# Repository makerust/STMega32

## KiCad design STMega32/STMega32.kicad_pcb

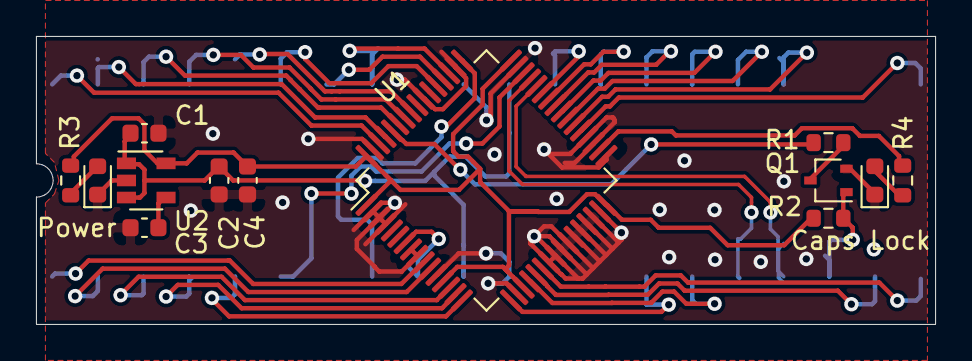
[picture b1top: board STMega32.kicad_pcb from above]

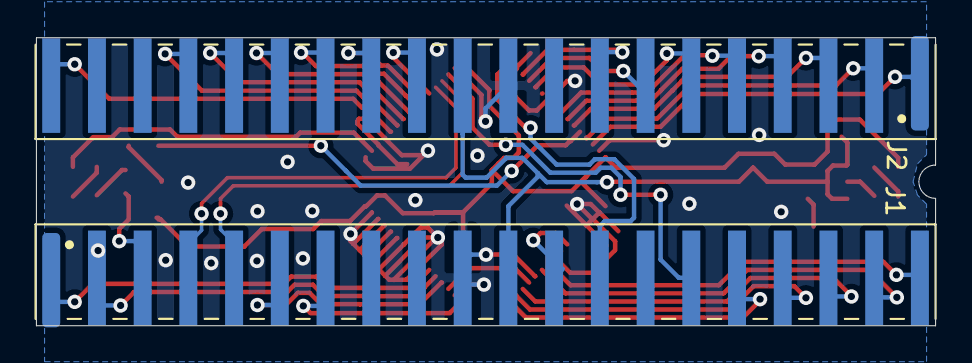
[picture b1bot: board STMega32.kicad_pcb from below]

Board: 2 copper layers, 49.9 x 16.0 mm, 15 parts (2 on the bottom side), 39 nets.

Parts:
C1, C4: 1uF; C_0603_1608Metric
C2, C3: 10nF; C_0603_1608Metric
Caps Lock: LED_ALT; LED_0603_1608Metric
J1, J2: Conn_01x20; Header_20Pin_90DegTHT_asSMD
Power: LED_ALT; LED_0603_1608Metric
Q1: 2SC4213; SOT-323_SC-70
R1, R2: 4k; R_0603_1608Metric
R3, R4: 560; R_0603_1608Metric
U1: STM32F072RBTx; LQFP-64_10x10mm_P0.5mm
U2: LD3985M33R_SOT23; SOT-23-5

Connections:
+3_3v: C4.1, R2.2, R3.1, U1.1, U1.13, U1.19, U1.32, U1.48, U1.64, U2.5
+5v: C1.1, C2.1, J1.11, J2.11, U2.1, U2.3
CAPS_LED: R4.1, U1.34
GND: C1.2, C2.2, C3.2, C4.2, Caps Lock.1, J1.10, J2.10, Power.1, Q1.2, U1.2, U1.3, U1.4, U1.8, U1.9, U1.12, U1.18, U1.23, U1.24, U1.25, U1.26, U1.27, U1.28, U1.29, U1.30, U1.31, U1.33, U1.35, U1.36, U1.47, U1.50, U1.55, U1.63, U2.2
MOSI: J1.15, U1.46
unnamed: C3.1, U2.4
unnamed: Power.2, R3.2
unnamed: Caps Lock.2, R4.2
unnamed: Q1.3, R1.1
Reset: J1.12, U1.7
SCK: J1.13, U1.49
USB_N: J1.4, U1.44
USB_P: J1.5, U1.45
boot: J1.3, Q1.1, R2.1
col0: J2.1, U1.62
col1: J1.20, U1.10
col2: J2.2, U1.61
col3: J1.19, U1.11
col4: J2.3, U1.59
col5: J1.18, U1.14
col6: J2.4, U1.58
col7: J1.17, U1.15
col8: J2.5, U1.57
col9: J1.16, U1.16
col10: J2.6, U1.53
col11: J2.7, U1.52
col12: J2.8, U1.51
col13: J1.1, U1.22
col14: J1.2, U1.21
col15: J1.6, U1.20
col16: J1.7, U1.17
col17: J2.20, U1.37
n_boot: R1.2, U1.60
row0: J2.17, U1.38
row1: J2.16, U1.39
row2: J2.12, U1.43
row3: J2.15, U1.40
row4: J2.13, U1.42
row5: J2.14, U1.41

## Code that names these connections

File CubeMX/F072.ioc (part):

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Mcu.Name=STM32F072R(8-B)Tx
Mcu.Package=LQFP64
Mcu.UserName=STM32F072RBTx
PA0.GPIOParameters=GPIO_Label
PA0.GPIO_Label=col5
PA0.Signal=GPIO_Input
PA1.GPIOParameters=GPIO_Label
PA1.GPIO_Label=col7
PA1.Signal=GPIO_Input
PA10.GPIOParameters=GPIO_Label
PA10.GPIO_Label=row2
PA10.Signal=GPIO_Output
PA11.Mode=Device
PA11.Signal=USB_DM
PA12.Mode=Device
PA12.Signal=USB_DP
PA13.Mode=Serial_Wire
PA13.Signal=SYS_SWDIO
PA14.Mode=Serial_Wire
PA14.Signal=SYS_SWCLK
PA2.GPIOParameters=GPIO_Label
PA2.GPIO_Label=col9
PA2.Signal=GPIO_Input
PA3.GPIOParameters=GPIO_Label
PA3.GPIO_Label=col16
PA3.Signal=GPIO_Input
PA4.GPIOParameters=GPIO_Label
PA4.GPIO_Label=col15
PA4.Signal=GPIO_Input
PA5.GPIOParameters=GPIO_Label
PA5.GPIO_Label=col14
PA5.Signal=GPIO_Input
PA6.GPIOParameters=GPIO_Label
PA6.GPIO_Label=col13
PA6.Signal=GPIO_Input
PA8.GPIOParameters=GPIO_Label
PA8.GPIO_Label=row5
PA8.Signal=GPIO_Input
PA9.GPIOParameters=GPIO_Label
PA9.GPIO_Label=row4
PA9.Signal=GPIO_Output
PB13.GPIOParameters=GPIO_Label
PB13.GPIO_Label=CAPS_LED
PB13.Signal=GPIO_Output
PB5.GPIOParameters=GPIO_Label
PB5.GPIO_Label=col8
PB5.Signal=GPIO_Input
PB6.GPIOParameters=GPIO_Label
PB6.GPIO_Label=col6
PB6.Signal=GPIO_Output
PB7.GPIOParameters=GPIO_Label
PB7.GPIO_Label=col4
PB7.Signal=GPIO_Input
PB8.GPIOParameters=GPIO_Label
PB8.GPIO_Label=col2
PB8.Signal=GPIO_Input
PB9.GPIOParameters=GPIO_Label
PB9.GPIO_Label=col0
PB9.Signal=GPIO_Input
PC1.GPIOParameters=GPIO_Label
PC1.GPIO_Label=col1
PC1.Signal=GPIO_Input
PC10.GPIOParameters=GPIO_Label
PC10.GPIO_Label=col12
PC10.Signal=GPIO_Input
PC11.GPIOParameters=GPIO_Label
PC11.GPIO_Label=col11
PC11.Signal=GPIO_Input
PC12.GPIOParameters=GPIO_Label
PC12.GPIO_Label=col10
PC12.Signal=GPIO_Input
PC2.GPIOParameters=GPIO_Label
PC2.GPIO_Label=col3
PC2.Signal=GPIO_Input
PC6.GPIOParameters=GPIO_Label
PC6.GPIO_Label=col17
PC6.Signal=GPIO_Input
PC7.GPIOParameters=GPIO_Label
PC7.GPIO_Label=row0
PC7.Signal=GPIO_Input
PC8.GPIOParameters=GPIO_Label
PC8.GPIO_Label=row1
PC8.Signal=GPIO_Input
PC9.GPIOParameters=GPIO_Label
PC9.GPIO_Label=row3
PC9.Signal=GPIO_Input
RCC.SYSCLKFreq_VALUE=48000000
RCC.SYSCLKSource=RCC_SYSCLKSOURCE_HSI48
board=custom

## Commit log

2021-04-15 festond commit
2021-04-15 corrected file inclusions
2021-04-15 Improved Ground, Tidied Silk
2021-04-21 added firmware with bad folder structure
2021-04-21 addid infor on README
2021-04-21 Add format
2021-04-21 Yet more format
2021-04-29 Changed microcontroller and rerouted to add ground integrity
2021-05-25 removed unused folder, changed R2 on inverter circuit to pullup
2021-05-25 clean up
2021-05-25 revamped the release folder, updated the Readme
